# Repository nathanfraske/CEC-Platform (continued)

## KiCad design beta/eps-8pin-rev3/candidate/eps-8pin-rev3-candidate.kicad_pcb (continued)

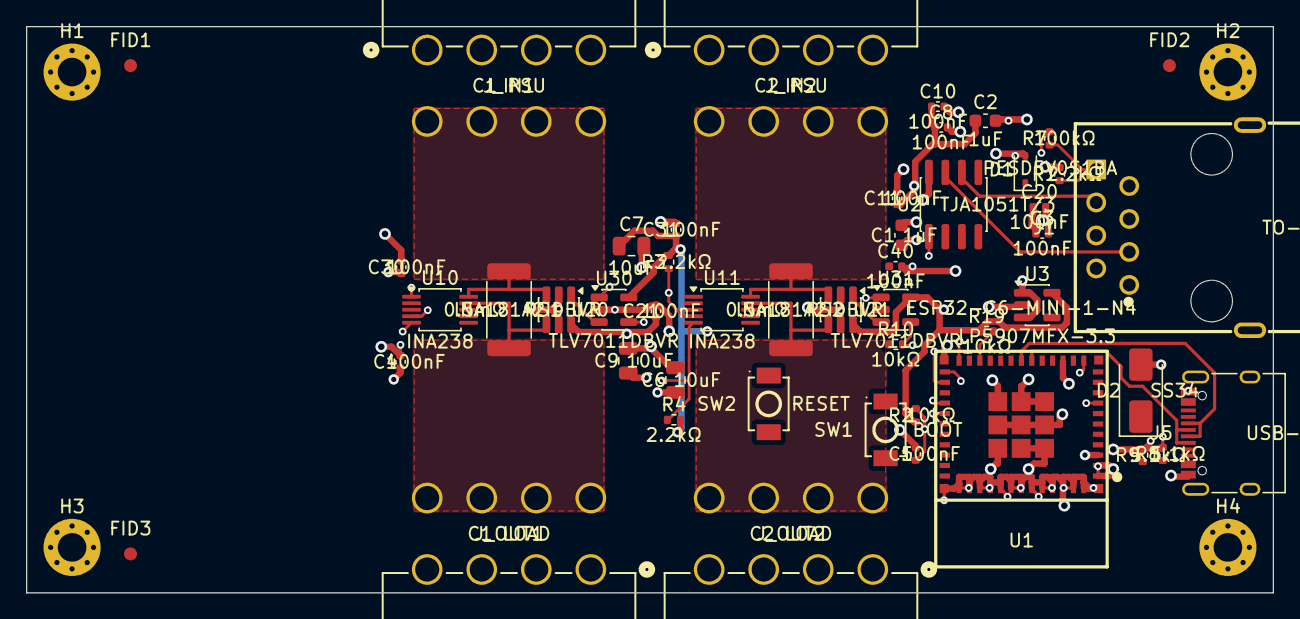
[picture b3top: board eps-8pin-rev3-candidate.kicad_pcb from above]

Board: 6 copper layers, 96.0 x 43.6 mm, 53 parts (0 on the bottom side), 29 nets.

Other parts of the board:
FID1, FID2, FID3: Fiducial_1mm_Mask2mm
H1, H2, H3, H4: MountingHole_2.2mm_M2_Pad_Via

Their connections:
GND: H1.1, H2.1, H3.1, H4.1; also elsewhere on the board

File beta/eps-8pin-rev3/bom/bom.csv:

Reference,Qty,Value,Footprint,MPN,Manufacturer,LCSC,LC_Stock,Chosen_Distributor,Datasheet,Validated,DNP,Notes
"C1,C2",2,1uF,C_0603_1608Metric,CL10A105KB8NNNC,Samsung,C15849,,,,,,
"C3,C4,C5,C8,C10,C11,C20,C21,C30,C31,C40",11,100nF,C_0402_1005Metric,CL05B104KO5NNNC,Samsung,C1525,,,,,,
"C6,C7,C9",3,10uF,C_0805_2012Metric,CL21A106KAYNNNE,Samsung,C15850,,,,,,
D1,1,PESD5V0S1BA,D_SOD-323,PESD5V0S1BA,HXY MOSFET,C5261083,,,https://www.lcsc.com/datasheet/C5261083.pdf,,,
D2,1,SS34,D_SMA,SS34,MDD,C8678,,,,,,
J1,1,TO-HUB,RJ45_FTP_Shielded_Horizontal,KH-RJ45-58-8P8C,Kinghelm,C2683360,,,https://www.lcsc.com/datasheet/C2683360.pdf,,,
J5,1,USB-C 2.0,USB_C_Receptacle_XKB_U262-16XN-4BVC11,U262-161N-4BVC11,XKB Connection,C319148,,,https://datasheet.lcsc.com/szlcsc/1811141824_XKB-Enterprise-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,,,
J_IN1,1,C1 PSU,Molex_Mini-Fit_Jr_87427-0802_2x04_P4.20mm_RA,87427-0802,Molex,,,,https://www.molex.com/content/dam/molex/molex-dot-com/produc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,,,
J_IN2,1,C2 PSU,Molex_Mini-Fit_Jr_87427-0802_2x04_P4.20mm_RA,87427-0802,Molex,,,,https://www.molex.com/content/dam/molex/molex-dot-com/produc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,,,
J_OUT1,1,C1 LOAD,Molex_Mini-Fit_Jr_87427-0802_2x04_P4.20mm_RA,87427-0802,Molex,,,,https://www.molex.com/content/dam/molex/molex-dot-com/produc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,,,
J_OUT2,1,C2 LOAD,Molex_Mini-Fit_Jr_87427-0802_2x04_P4.20mm_RA,87427-0802,Molex,,,,https://www.molex.com/content/dam/molex/molex-dot-com/produc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,,,
"R1,R3,R4",3,2.2kΩ,R_0402_1005Metric,0402WGF2201TCE,UNI-ROYAL,C25879,,,,,,
"R2,R10,R19",3,10kΩ,R_0402_1005Metric,0402WGF1002TCE,UNI-ROYAL,C25744,,,https://www.lcsc.com/product-detail/C25744.html,,,10 kohm follows Espressif ESP32-C6-DevKitC-1; GPIO8 must be high with GPIO9 low for joint download boot
R7,1,100kΩ,R_0402_1005Metric,0402WGF1003TCE,UNI-ROYAL,C25741,,,,,,
"R8,R9",2,5.1kΩ,R_0402_1005Metric,0402WGF5101TCE,UNI-ROYAL,C25905,,,,,,
"RS1,RS2",2,0.5mΩ,R_2512_6332Metric,CSS2H-2512R-L500F,Bourns,,,,https://www.bourns.com/docs/product-datasheets/css2h-2512.pdf,,,"OQ-11 locked selection on the single current EPS product: 0.5mOhm, CSS2H-2512R-L500F. Distributor availability remains a BOM-freeze check."
SW1,1,BOOT,TS-1088-AR02016,TS-1088-AR02016,XUNPU,C720477,,,https://www.lcsc.com/datasheet/C720477.pdf,,,
SW2,1,RESET,TS-1088-AR02016,TS-1088-AR02016,XUNPU,C720477,,,https://www.lcsc.com/datasheet/C720477.pdf,,,
U1,1,ESP32-C6-MINI-1-N4,ESP32-C6-MINI-1,ESP32-C6-MINI-1-N4,Espressif Systems,C5736265,,,https://documentation.espressif.com/esp32-c6-mini-1_mini-1u_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,,,
"U10,U11",2,INA238,VSSOP-10_3x3mm_P0.5mm,INA238AIDGSR,Texas Instruments,C2868250,,,https://www.ti.com/lit/ds/symlink/ina238.pdf,,,
U2,1,TJA1051T/3,SOIC-8_3.9x4.9mm_P1.27mm,TJA1051T/3/1J,NXP Semiconductors,C38695,,,https://www.nxp.com/docs/en/data-sheet/TJA1051.pdf,,,
"U20,U21",2,INA181A2IDBVR,SOT-23-6,INA181A2IDBVR,Texas Instruments,C2058784,,,https://www.ti.com/lit/ds/symlink/ina181.pdf,,,
U3,1,LP5907MFX-3.3,SOT-23-5,LP5907MFX-3.3/NOPB,Texas Instruments,C80670,,,https://www.ti.com/lit/ds/symlink/lp5907.pdf,,,
"U30,U31",2,TLV7011DBVR,SOT-23-5,TLV7011DBVR,Texas Instruments,C702117,,,https://www.ti.com/lit/ds/symlink/tlv7011.pdf,,,

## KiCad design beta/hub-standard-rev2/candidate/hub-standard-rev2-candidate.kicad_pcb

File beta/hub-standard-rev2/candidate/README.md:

# `candidate/`: the current best diagnostic board for this module

ONE board file, kept current by the wave (owner directive 2026-07-25: "the current
best should be placed into a candidate folder per board and kept current with only
one board ideally so we have a reference").

`<board>-candidate.kicad_pcb` (+ its `.kicad_pro` / `.kicad_dru` sidecars) is a COPY
of the best board the wave has ever published for this module, with `candidate.json`
recording where it came from and how it graded. Open it to see the real current
state of the layout without digging through `build/fresh-wave-*/`.

IMPORTANT: `candidate/` is a diagnostic-reference channel, not a release-acceptance
channel. A routed board remains here when its route gate fails so reviewers can see
and improve the best failure. `candidate.json` therefore records
`candidate_role: diagnostic-reference`, `release_accepted: false`, and the distinct
`route_gate_passed` result. Only the aggregate release pipeline may accept a board.

RULES the wave enforces on every publish:
  * SCHEMATIC FRESHNESS outranks score: a winner matching more of the CURRENT
    component signatures replaces the reference even on a worse score, and a
    staler board never replaces a fresher one. The signature covers value,
    footprint, and numbered-pad nets. `schematic_match` and `schematic_exact` in
    `candidate.json` record the result. A board that grades well but predates a
    schematic or footprint change is the worse reference;
  * otherwise it replaces this file only when the new winner BEATS the recorded
    `sort_key` (lower is better -- the same ranking the wave itself uses);
  * a board satisfying the CURRENT segmented-mezzanine geometry replaces one
    that violates it, independent of route score; an obsolete mechanical datum
    is stale in the same way an obsolete component signature is stale;
  * a routed winner always beats a placement-only one, and a placement-only winner
    NEVER overwrites a routed reference;
  * exactly one `.kicad_pcb` lives here -- stale board files are pruned.

`candidate.json` is also refreshable without publishing a board. Consumers that
use a candidate as a placement oracle or materialization template MUST require
`schematic_exact: true` after a current refresh. A stale candidate remains useful
for historical outline, connector, mount, and copper review, but it is not a
component-inventory or pin/net authority.

This is a REFERENCE, not the board of record: it is machine-written, so never hand-edit
it (edits are silently overwritten by the next better wave). The authoritative
schematic + the module's own project files stay in the parent directory.

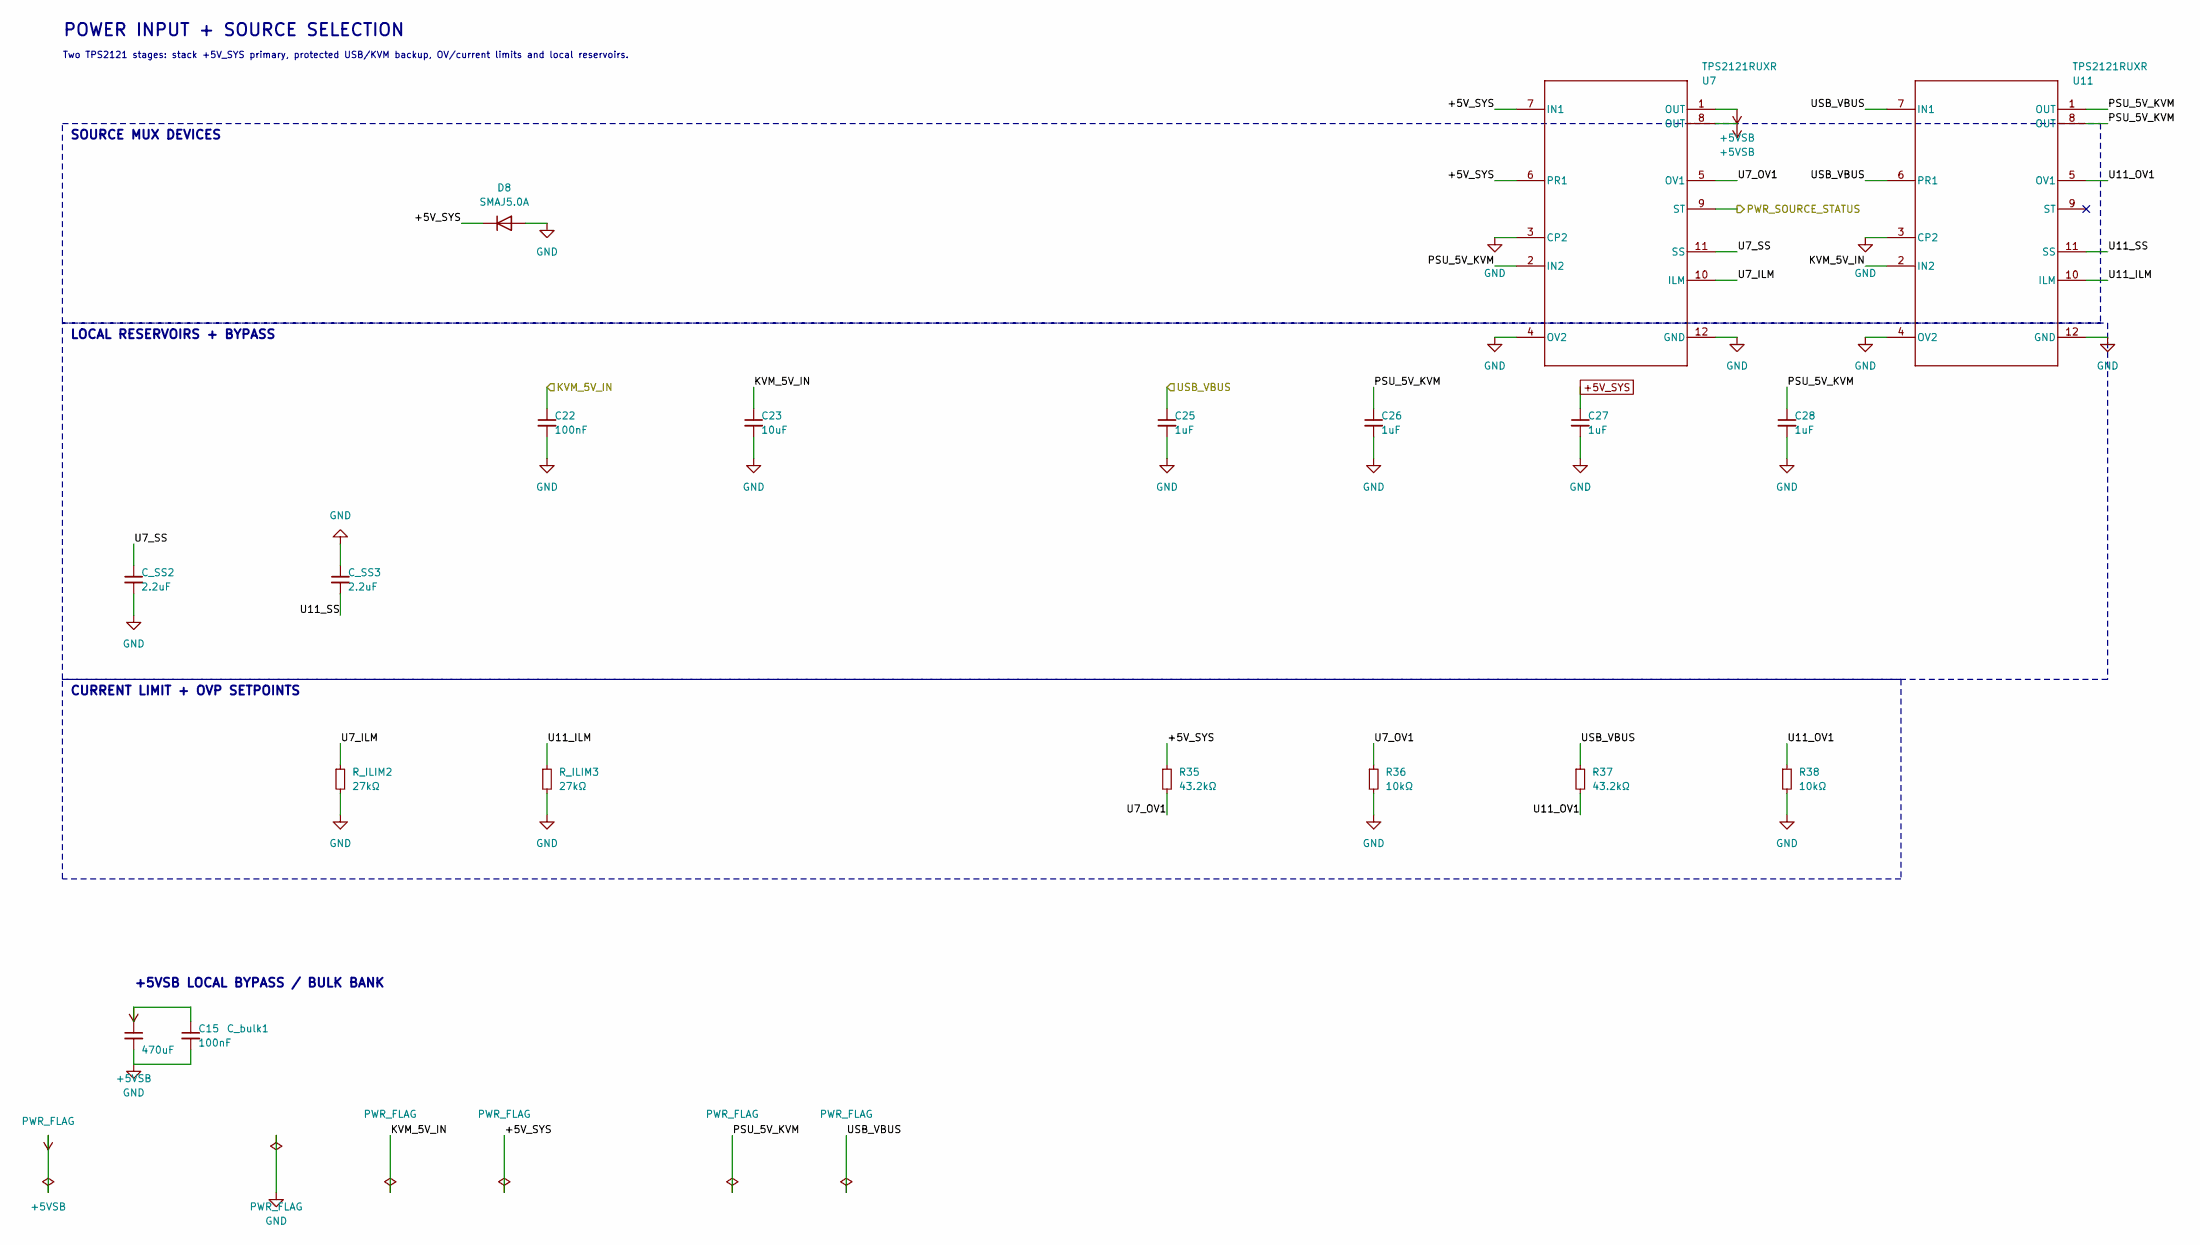
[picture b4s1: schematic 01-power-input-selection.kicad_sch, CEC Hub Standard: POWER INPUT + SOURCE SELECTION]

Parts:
C15, C22: 100nF; C_0402_1005Metric; MPN CL05B104KO5NNNC; LCSC C1525
C23: 10uF; C_0603_1608Metric; MPN CL10A106MA8NRNC; LCSC C96446
C25, C26, C27, C28: 1uF; C_0603_1608Metric; MPN CL10A105KB8NNNC; LCSC C15849
C_SS2, C_SS3: 2.2uF; C_0603_1608Metric; MPN CL10A225KO8NNNC; LCSC C23630
C_bulk1: 470uF; CP_Elec_6.3x7.7; MPN RVT1A471M0607; LCSC C335982
D8: SMAJ5.0A; D_SMA; MPN SMAJ5.0A; LCSC C113952
R35, R37: 43.2kΩ; R_0402_1005Metric; MPN 0402WGF4322TCE; LCSC C25894
R36, R38: 10kΩ; R_0402_1005Metric; MPN 0402WGF1002TCE; LCSC C25744
R_ILIM2, R_ILIM3: 27kΩ; R_0402_1005Metric; MPN 0402WGF2702TCE; LCSC C25771
U7, U11: TPS2121RUXR; RUX0012A; MPN TPS2121RUXR; LCSC C485916

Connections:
+5VSB: C15.1, C_bulk1.1, U7.1 (OUT), U7.8 (OUT); also elsewhere on the board
+5V_SYS: C27.1, D8.1 (K), R35.1, U7.6 (PR1), U7.7 (IN1); also elsewhere on the board
/KVM_5V_IN: C22.1, C23.1, U11.2 (IN2); also elsewhere on the board
/POWER INPUT + SOURCE SELECTION/PSU_5V_KVM: C26.1, C28.1, U7.2 (IN2), U11.1 (OUT), U11.8 (OUT)
/POWER INPUT + SOURCE SELECTION/U7_ILM: R_ILIM2.1, U7.10 (ILM)
/POWER INPUT + SOURCE SELECTION/U7_OV1: R35.2, R36.1, U7.5 (OV1)
/POWER INPUT + SOURCE SELECTION/U7_SS: C_SS2.1, U7.11 (SS)
/POWER INPUT + SOURCE SELECTION/U11_ILM: R_ILIM3.1, U11.10 (ILM)
/POWER INPUT + SOURCE SELECTION/U11_OV1: R37.2, R38.1, U11.5 (OV1)
/POWER INPUT + SOURCE SELECTION/U11_SS: C_SS3.2, U11.11 (SS)
/PWR_SOURCE_STATUS: U7.9 (ST); also elsewhere on the board
/USB_VBUS: C25.1, R37.1, U11.6 (PR1), U11.7 (IN1); also elsewhere on the board

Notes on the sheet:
POWER INPUT + SOURCE SELECTION
Two TPS2121 stages: stack +5V_SYS primary, protected USB/KVM backup, OV/current limits and local reservoirs.
+5VSB LOCAL BYPASS / BULK BANK
SOURCE MUX DEVICES
LOCAL RESERVOIRS + BYPASS
CURRENT LIMIT + OVP SETPOINTS

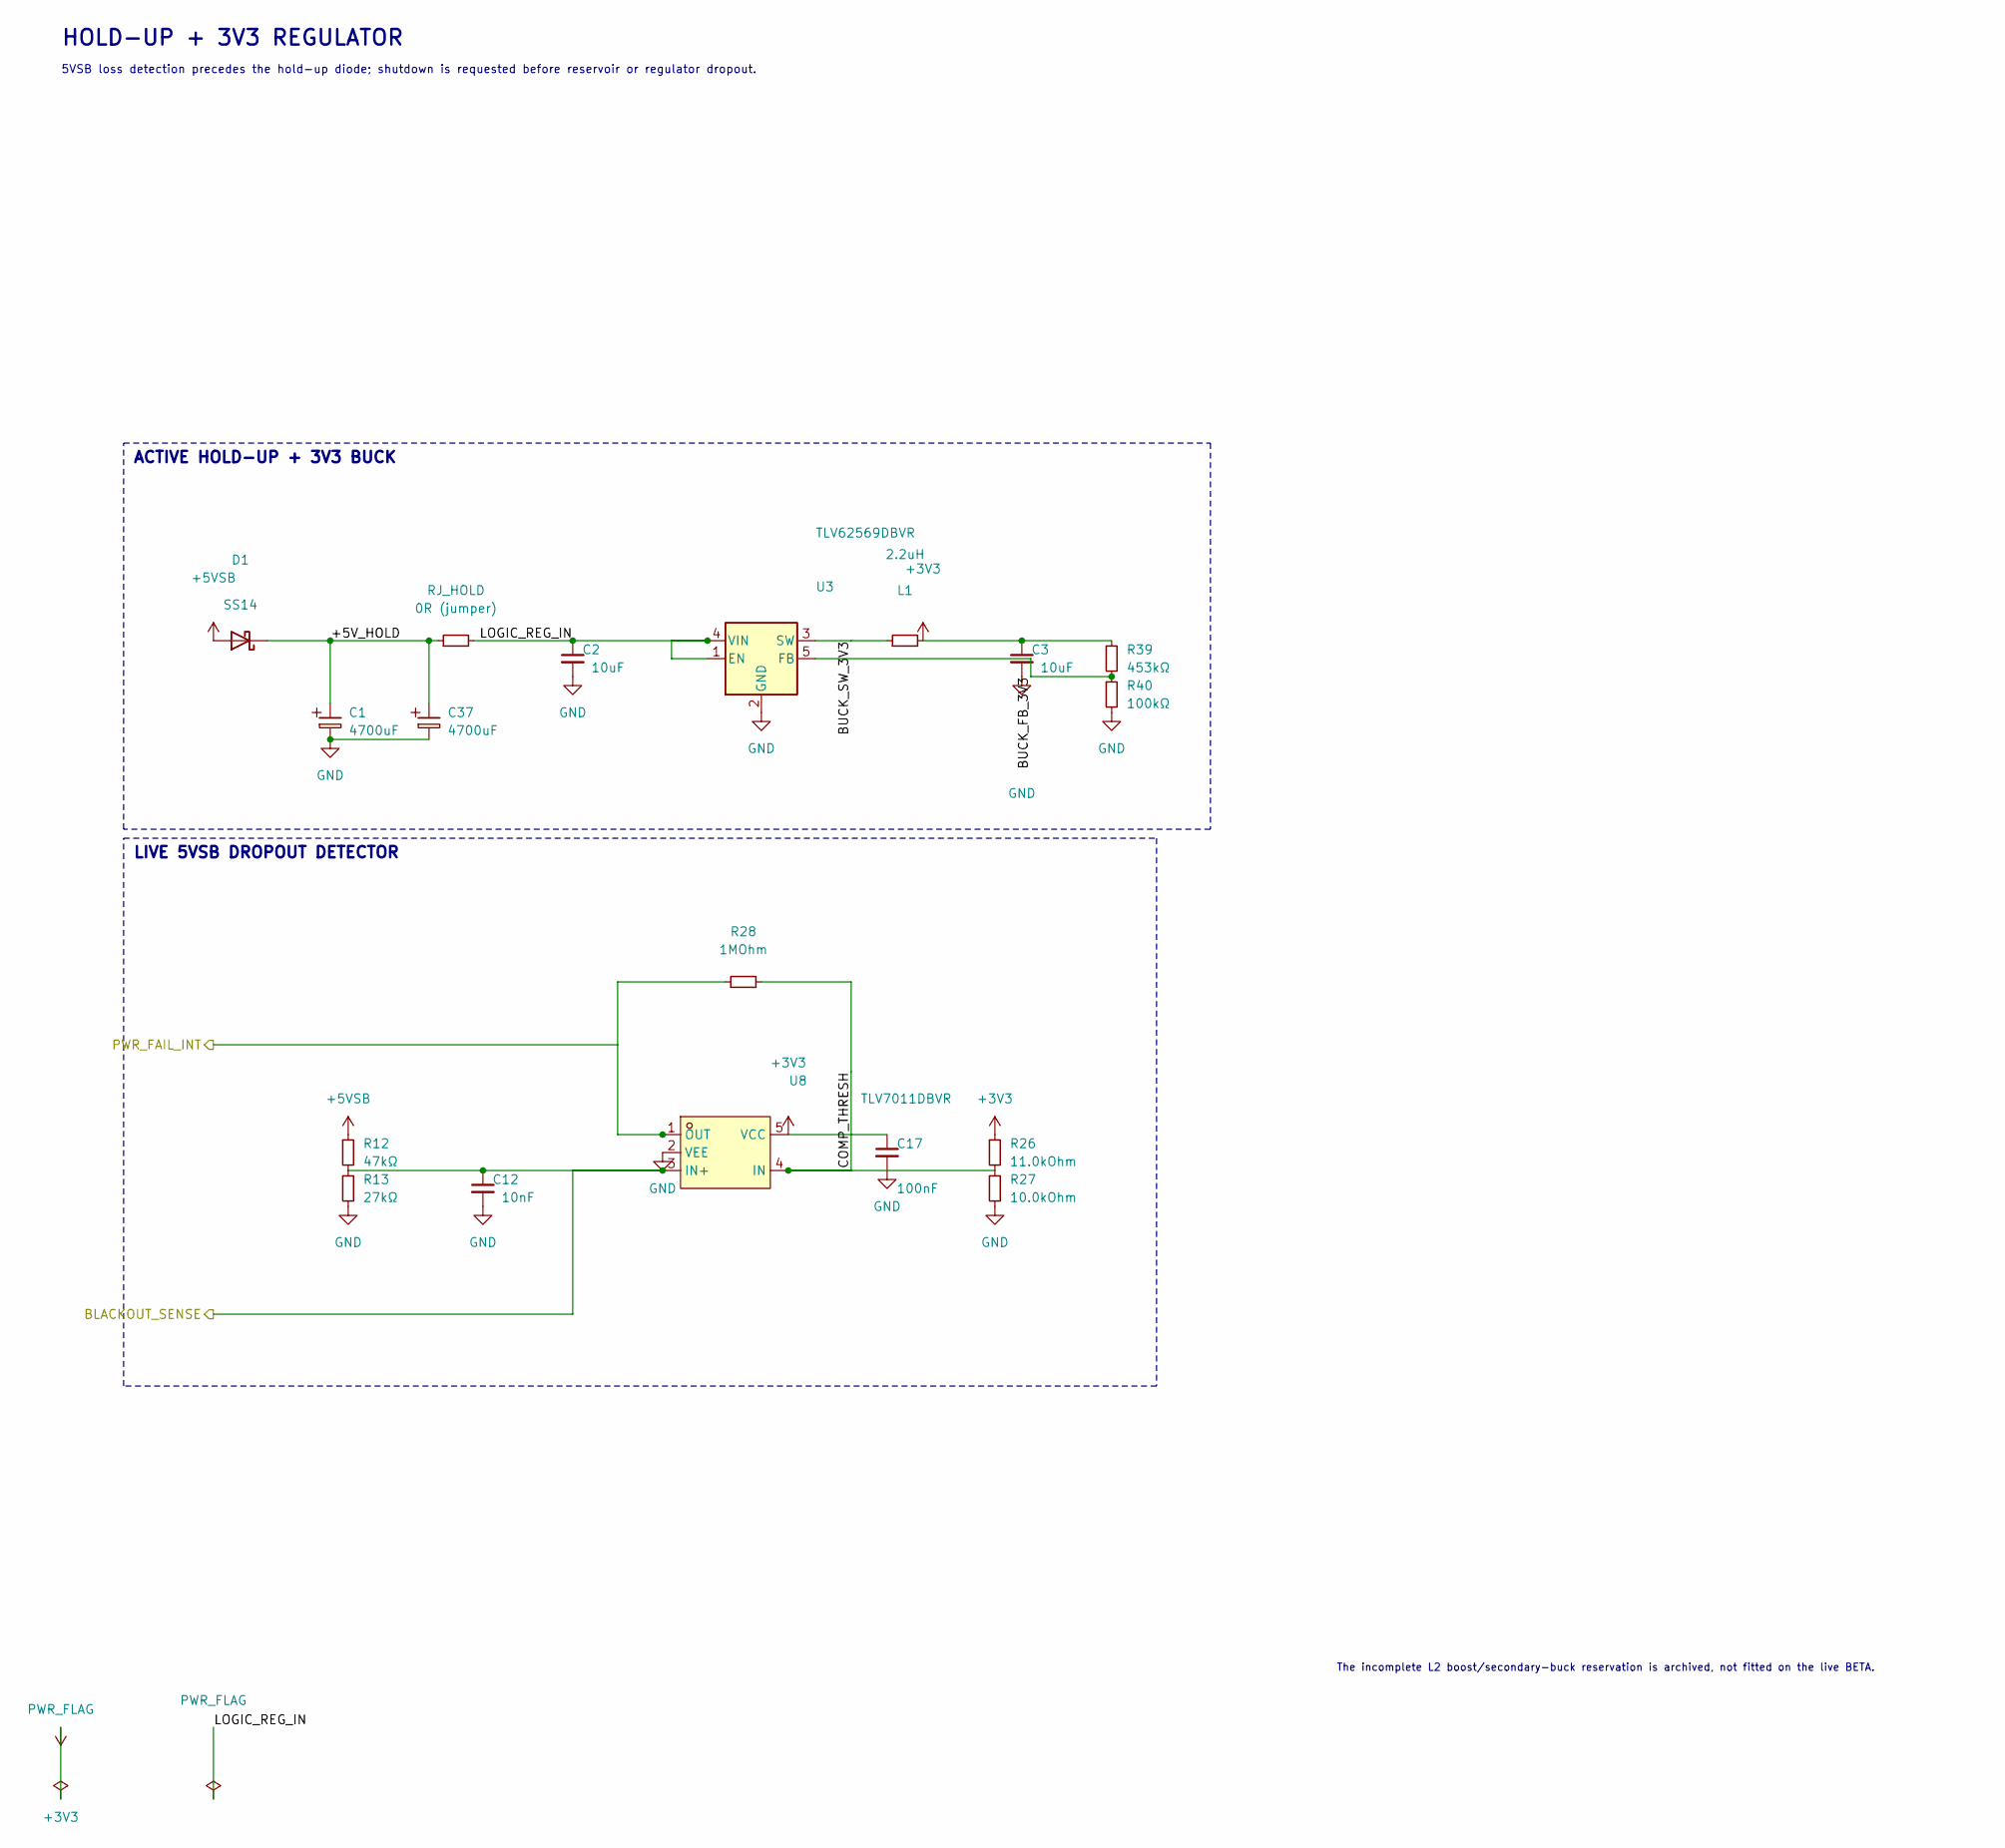
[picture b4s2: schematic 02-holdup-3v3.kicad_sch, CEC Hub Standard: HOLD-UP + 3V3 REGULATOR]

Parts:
C1, C37: 4700uF; CP_Elec_Lelon_VZH_18x16.5; MPN VZH472M1CTR-1816; LCSC C249940
C2, C3: 10uF; C_0603_1608Metric; MPN CL10A106MA8NRNC; LCSC C96446
C12: 10nF; C_0402_1005Metric; MPN CL05B103KB5NNNC; LCSC C15195
C17: 100nF; C_0402_1005Metric; MPN CL05B104KO5NNNC; LCSC C1525
D1: SS14; D_SMA; MPN SS14; LCSC C2480
L1: 2.2uH; VLS252010HBX-2R2M-1; MPN VLS252010HBX-2R2M-1; LCSC C88527
R12: 47kΩ; R_0402_1005Metric; MPN 0402WGF4702TCE; LCSC C25792
R13: 27kΩ; R_0402_1005Metric; MPN 0402WGF2702TCE; LCSC C25771
R26: 11.0kOhm; R_0402_1005Metric; MPN RC0402FR-0711KL; LCSC C138063
R27: 10.0kOhm; R_0402_1005Metric; MPN 0402WGF1002TCE; LCSC C25744
R28: 1MOhm; R_0402_1005Metric; MPN 0402WGF1004TCE; LCSC C26083
R39: 453kΩ; R_0402_1005Metric; MPN 0402WGF4533TCE; LCSC C27009
R40: 100kΩ; R_0402_1005Metric; MPN 0402WGF1003TCE; LCSC C25741
RJ_HOLD: 0R (jumper); R_0402_1005Metric; MPN 0402WGF0000TCE; LCSC C17168
U3: TLV62569DBVR; SOT-23-5_L3.0-W1.7-P0.95-LS2.8-BL; MPN TLV62569DBVR; LCSC C141836
U8: TLV7011DBVR; SOT-23-5; MPN TLV7011DBVR; LCSC C702117

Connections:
+3V3: C3.1, C17.1, L1.2, R26.1, R39.1, U8.5 (VCC); also elsewhere on the board
+5VSB: D1.2 (A), R12.1; also elsewhere on the board
/BLACKOUT_SENSE: C12.1, R12.2, R13.1, U8.3 (IN+); also elsewhere on the board
/HOLD-UP + 3V3 REGULATOR/+5V_HOLD: C1.1 (+), C37.1 (+), D1.1 (K), RJ_HOLD.1
/HOLD-UP + 3V3 REGULATOR/BUCK_FB_3V3: R39.2, R40.1, U3.5 (FB)
/HOLD-UP + 3V3 REGULATOR/BUCK_SW_3V3: L1.1, U3.3 (SW)
/HOLD-UP + 3V3 REGULATOR/LOGIC_REG_IN: C2.1, RJ_HOLD.2, U3.1 (EN), U3.4 (VIN)
/PWR_FAIL_INT: R28.1, U8.1 (OUT); also elsewhere on the board

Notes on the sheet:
HOLD-UP + 3V3 REGULATOR
5VSB loss detection precedes the hold-up diode; shutdown is requested before reservoir or regulator dropout.
The incomplete L2 boost/secondary-buck reservation is archived, not fitted on the live BETA.
ACTIVE HOLD-UP + 3V3 BUCK
LIVE 5VSB DROPOUT DETECTOR

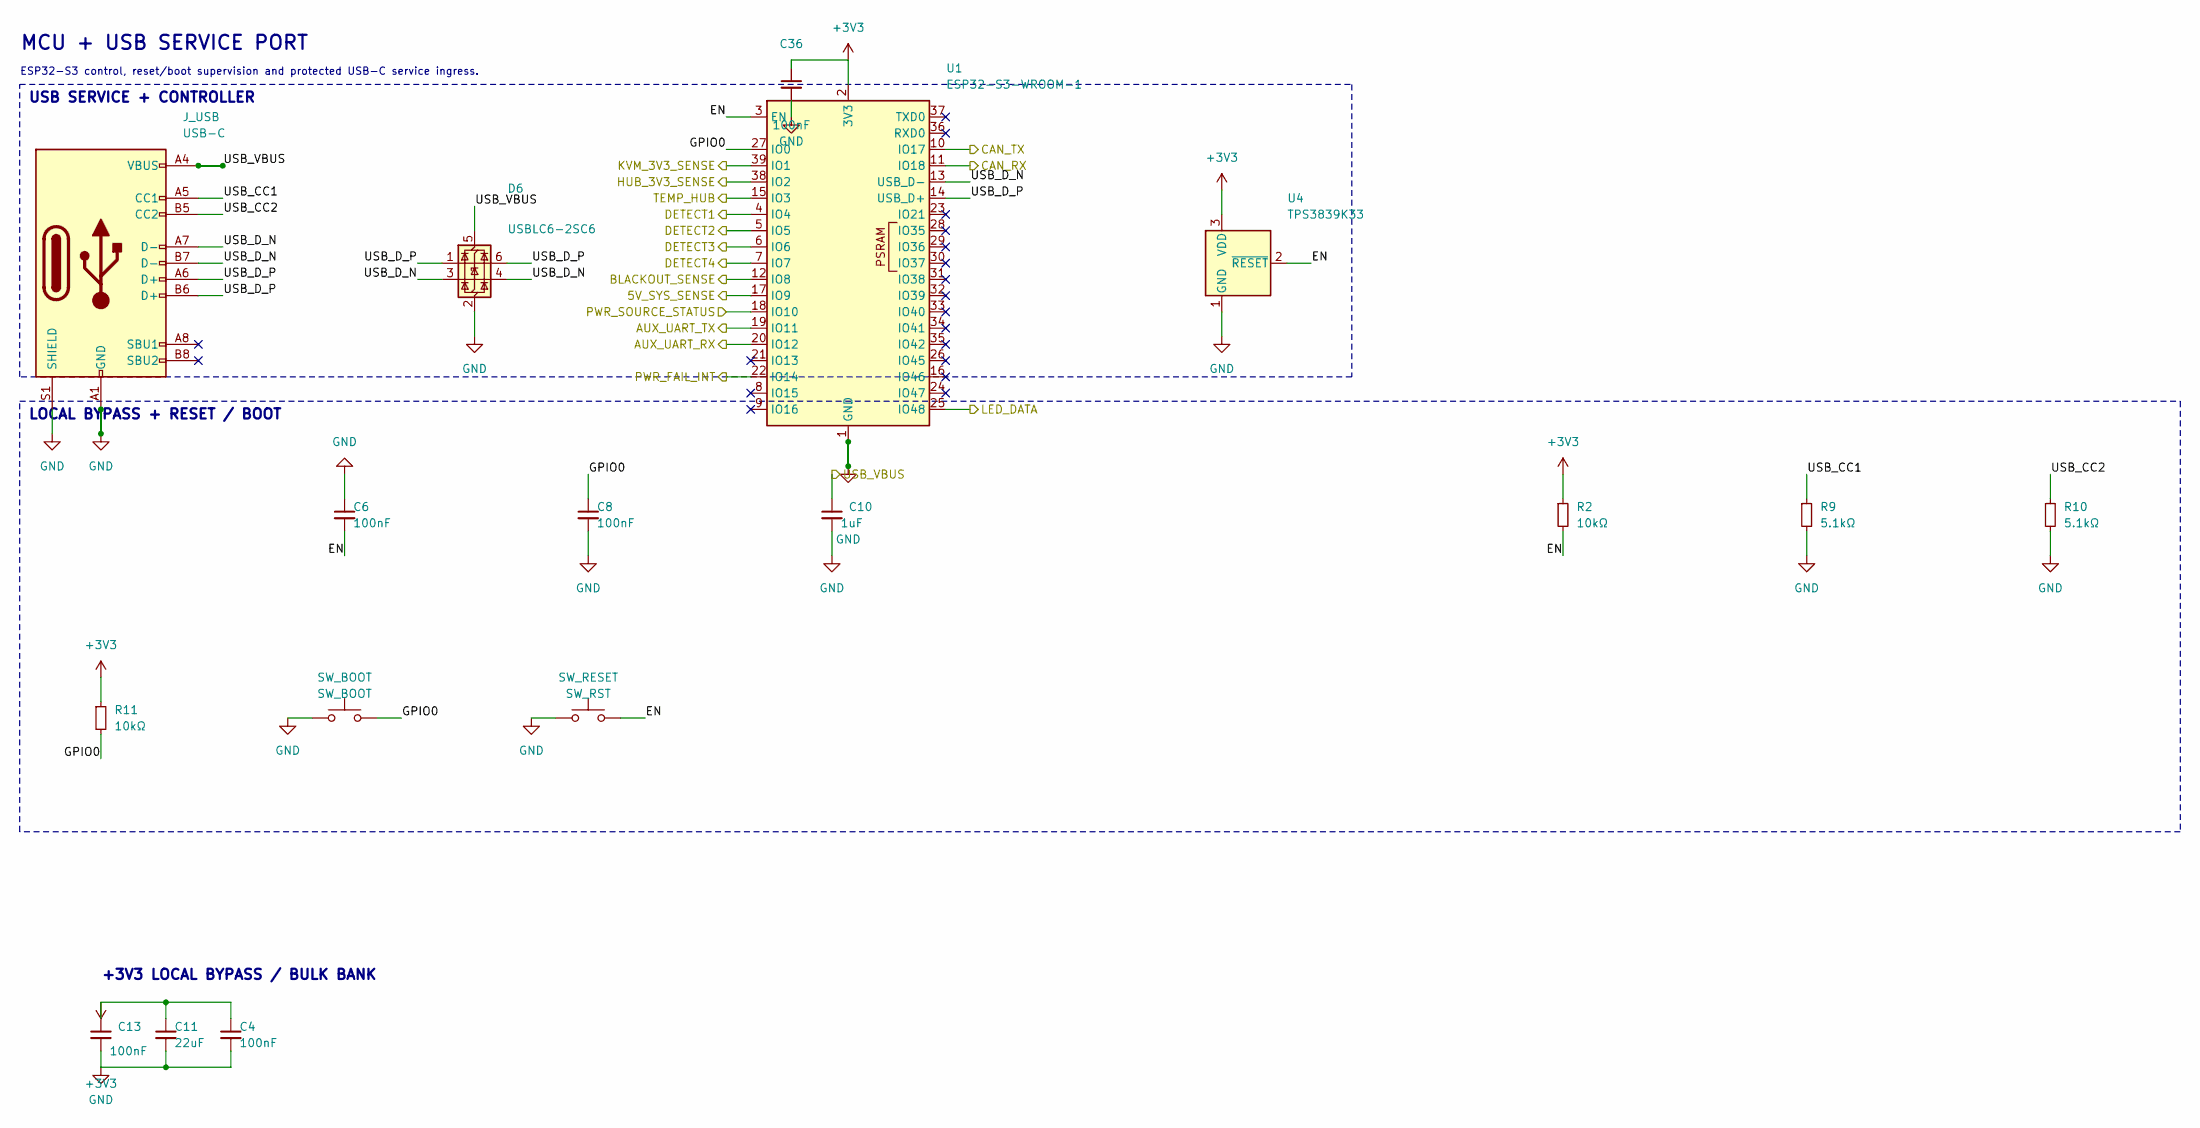
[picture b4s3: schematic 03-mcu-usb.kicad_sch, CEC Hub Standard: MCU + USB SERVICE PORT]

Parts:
C4, C6, C8, C13, C36: 100nF; C_0402_1005Metric; MPN CL05B104KO5NNNC; LCSC C1525
C10: 1uF; C_0603_1608Metric; MPN CL10A105KB8NNNC; LCSC C15849
C11: 22uF; C_0603_1608Metric; MPN CL10A226MP8NUNE; LCSC C86295
D6: USBLC6-2SC6; SOT-23-6; MPN USBLC6-2SC6; LCSC C2687116
J_USB: USB-C; USB_C_Receptacle_GCT_USB4215-03-A; MPN USB4215-03-A; LCSC C37616412
R2, R11: 10kΩ; R_0402_1005Metric; MPN 0402WGF1002TCE; LCSC C25744
R9, R10: 5.1kΩ; R_0402_1005Metric; MPN 0402WGF5101TCE; LCSC C25905
SW_BOOT: SW_BOOT; TS-1088-AR02016; MPN TS-1088-AR02016; LCSC C720477
SW_RESET: SW_RST; TS-1088-AR02016; MPN TS-1088-AR02016; LCSC C720477
U1: ESP32-S3-WROOM-1; ESP32-S3-WROOM-1_NoAntKeepout; MPN ESP32-S3-WROOM-1-N16R8; LCSC C2913202
U4: TPS3839K33; SOT-23; MPN TPS3839K33DBZR; LCSC C96333

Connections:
+3V3: C4.1, C11.1, C13.1, C36.1, R2.1, R11.1, U1.2 (3V3), U4.3 (VDD); also elsewhere on the board
/5V_SYS_SENSE: U1.17 (IO9); also elsewhere on the board
/AUX_UART_RX: U1.20 (IO12); also elsewhere on the board
/AUX_UART_TX: U1.19 (IO11); also elsewhere on the board
/BLACKOUT_SENSE: U1.12 (IO8); also elsewhere on the board
/CAN_RX: U1.11 (IO18); also elsewhere on the board
/CAN_TX: U1.10 (IO17); also elsewhere on the board
/DETECT1: U1.4 (IO4); also elsewhere on the board
/DETECT2: U1.5 (IO5); also elsewhere on the board
/DETECT3: U1.6 (IO6); also elsewhere on the board
/DETECT4: U1.7 (IO7); also elsewhere on the board
/HUB_3V3_SENSE: U1.38 (IO2); also elsewhere on the board
/KVM_3V3_SENSE: U1.39 (IO1); also elsewhere on the board
/LED_DATA: U1.25 (IO48); also elsewhere on the board
/MCU + USB SERVICE PORT/EN: C6.2, R2.2, SW_RESET.2, U1.3 (EN), U4.2 (~RESET)
/MCU + USB SERVICE PORT/GPIO0: C8.1, R11.2, SW_BOOT.2, U1.27 (IO0)
/MCU + USB SERVICE PORT/USB_CC1: J_USB.A5 (CC1), R9.1
/MCU + USB SERVICE PORT/USB_CC2: J_USB.B5 (CC2), R10.1
/MCU + USB SERVICE PORT/USB_D_N: D6.3 (I/O2), D6.4 (I/O2), J_USB.A7 (D-), J_USB.B7 (D-), U1.13 (USB_D-)
/MCU + USB SERVICE PORT/USB_D_P: D6.1 (I/O1), D6.6 (I/O1), J_USB.A6 (D+), J_USB.B6 (D+), U1.14 (USB_D+)
/PWR_FAIL_INT: U1.22 (IO14); also elsewhere on the board
/PWR_SOURCE_STATUS: U1.18 (IO10); also elsewhere on the board
/TEMP_HUB: U1.15 (IO3); also elsewhere on the board
/USB_VBUS: C10.1, D6.5 (VBUS), J_USB.A4 (VBUS), J_USB.A9 (VBUS), J_USB.B4 (VBUS), J_USB.B9 (VBUS); also elsewhere on the board

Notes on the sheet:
MCU + USB SERVICE PORT
ESP32-S3 control, reset/boot supervision and protected USB-C service ingress.
+3V3 LOCAL BYPASS / BULK BANK
USB SERVICE + CONTROLLER
LOCAL BYPASS + RESET / BOOT

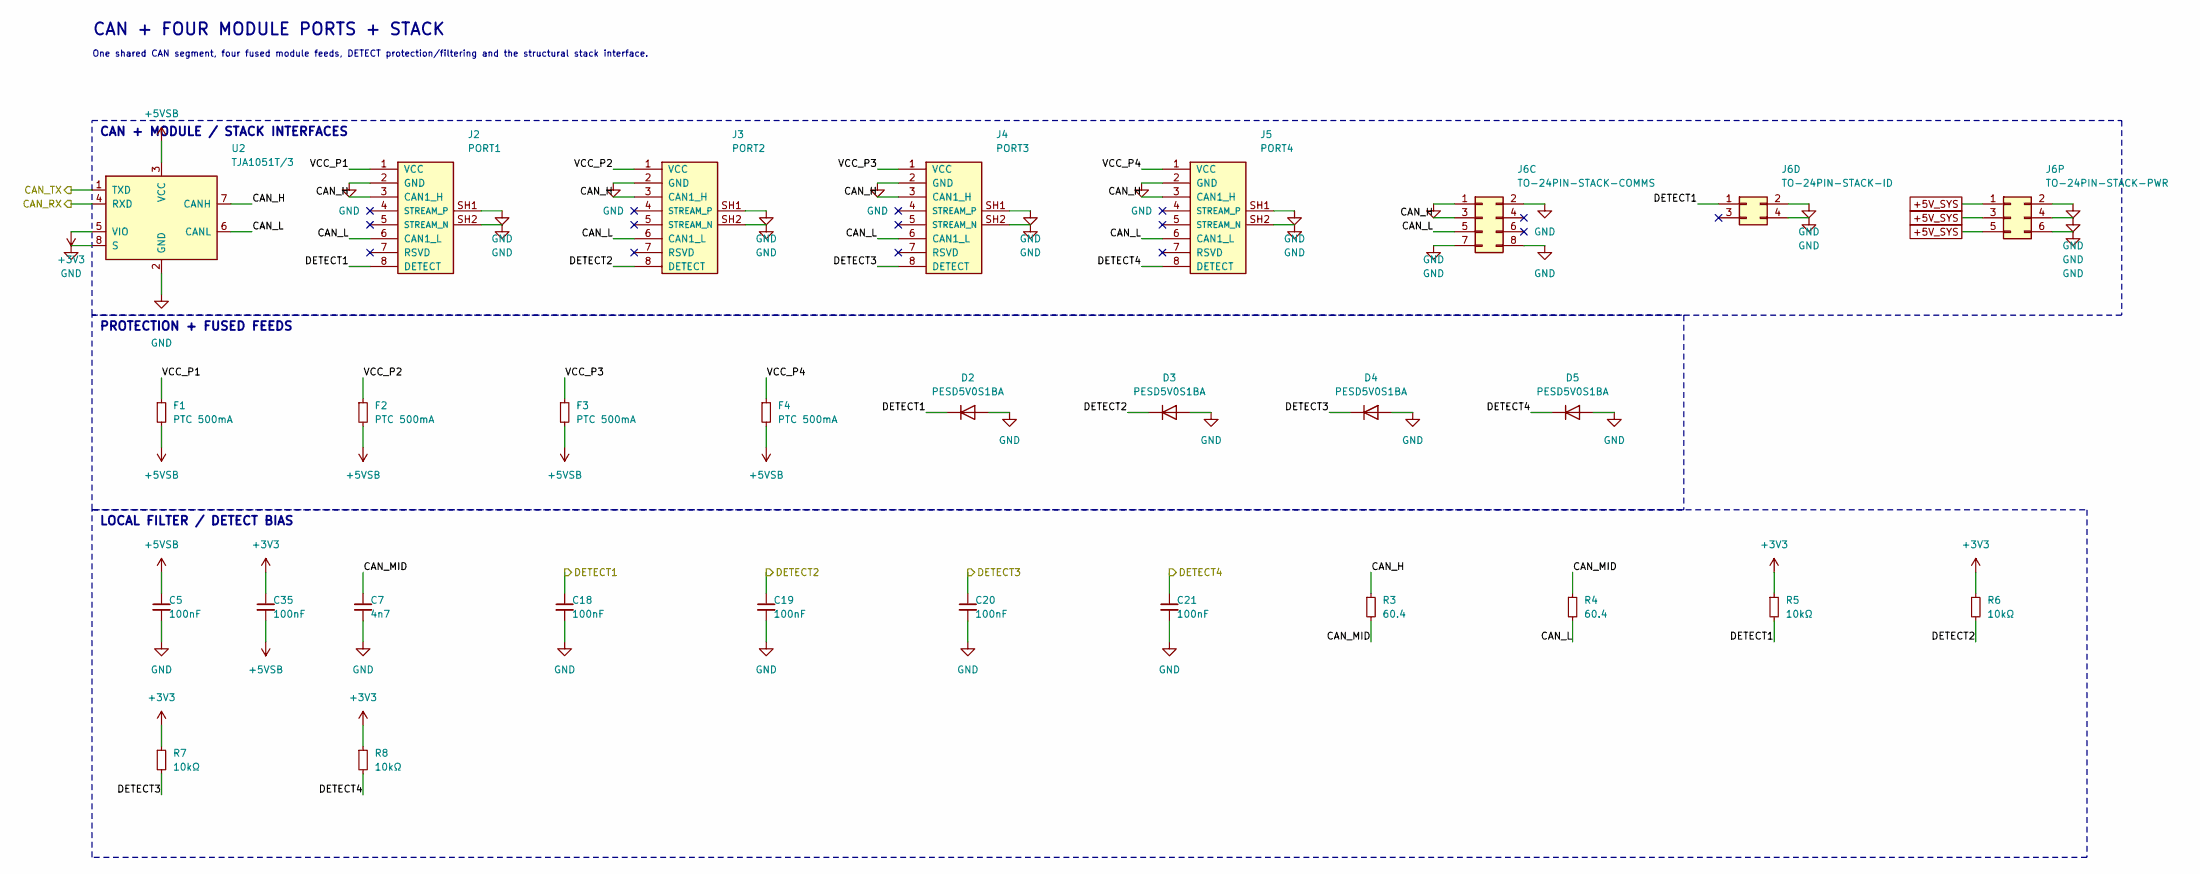
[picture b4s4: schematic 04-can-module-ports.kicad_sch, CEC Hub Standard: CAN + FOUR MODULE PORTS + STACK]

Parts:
C5, C18, C19, C20, C21, C35: 100nF; C_0402_1005Metric; MPN CL05B104KO5NNNC; LCSC C1525
C7: 4n7; C_0402_1005Metric; MPN 0402B472K500NT; LCSC C1538
D2, D3, D4, D5: PESD5V0S1BA; D_SOD-323; MPN PESD5V0S1BA; LCSC C5261083
F1, F2, F3, F4: PTC 500mA; R_0805_2012Metric; MPN SMD0805-050-6; LCSC C46640983
J2: PORT1; RJ45_FTP_Shielded_Horizontal; MPN KH-RJ45-58-8P8C; LCSC C2683360
J3: PORT2; RJ45_FTP_Shielded_Horizontal; MPN KH-RJ45-58-8P8C; LCSC C2683360
J4: PORT3; RJ45_FTP_Shielded_Horizontal; MPN KH-RJ45-58-8P8C; LCSC C2683360
J5: PORT4; RJ45_FTP_Shielded_Horizontal; MPN KH-RJ45-58-8P8C; LCSC C2683360
J6C: TO-24PIN-STACK-COMMS; PinSocket_2x04_P2.54mm_Vertical; MPN SSQ-104-01-G-D
J6D: TO-24PIN-STACK-ID; PinSocket_2x02_P2.54mm_Vertical; MPN SSQ-102-01-G-D
J6P: TO-24PIN-STACK-PWR; PinSocket_2x03_P2.54mm_Vertical; MPN SSQ-103-01-G-D
R3, R4: 60.4; R_0402_1005Metric; MPN GR0402F60R4TAG00; LCSC C49654185
R5, R6, R7, R8: 10kΩ; R_0402_1005Metric; MPN 0402WGF1002TCE; LCSC C25744
U2: TJA1051T/3; SOIC-8_3.9x4.9mm_P1.27mm; MPN TJA1051T/3/1J; LCSC C38695

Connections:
+3V3: C35.1, R5.1, R6.1, R7.1, R8.1, U2.5 (VIO); also elsewhere on the board
+5VSB: C5.1, C35.2, F1.2, F2.2, F3.2, F4.2, U2.3 (VCC); also elsewhere on the board
+5V_SYS: J6P.1, J6P.3, J6P.5; also elsewhere on the board
/CAN + FOUR MODULE PORTS + STACK/CAN_H: J2.3 (CAN1_H), J3.3 (CAN1_H), J4.3 (CAN1_H), J5.3 (CAN1_H), J6C.3, R3.1, U2.7 (CANH)
/CAN + FOUR MODULE PORTS + STACK/CAN_L: J2.6 (CAN1_L), J3.6 (CAN1_L), J4.6 (CAN1_L), J5.6 (CAN1_L), J6C.5, R4.2, U2.6 (CANL)
/CAN + FOUR MODULE PORTS + STACK/CAN_MID: C7.1, R3.2, R4.1
/CAN + FOUR MODULE PORTS + STACK/VCC_P1: F1.1, J2.1 (VCC)
/CAN + FOUR MODULE PORTS + STACK/VCC_P2: F2.1, J3.1 (VCC)
/CAN + FOUR MODULE PORTS + STACK/VCC_P3: F3.1, J4.1 (VCC)
/CAN + FOUR MODULE PORTS + STACK/VCC_P4: F4.1, J5.1 (VCC)
/CAN_RX: U2.4 (RXD); also elsewhere on the board
/CAN_TX: U2.1 (TXD); also elsewhere on the board
/DETECT1: C18.1, D2.1 (K), J2.8 (DETECT), J6D.1, R5.2; also elsewhere on the board
/DETECT2: C19.1, D3.1 (K), J3.8 (DETECT), R6.2; also elsewhere on the board
/DETECT3: C20.1, D4.1 (K), J4.8 (DETECT), R7.2; also elsewhere on the board
/DETECT4: C21.1, D5.1 (K), J5.8 (DETECT), R8.2; also elsewhere on the board

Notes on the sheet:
CAN + FOUR MODULE PORTS + STACK
One shared CAN segment, four fused module feeds, DETECT protection/filtering and the structural stack interface.
CAN + MODULE / STACK INTERFACES
PROTECTION + FUSED FEEDS
LOCAL FILTER / DETECT BIAS

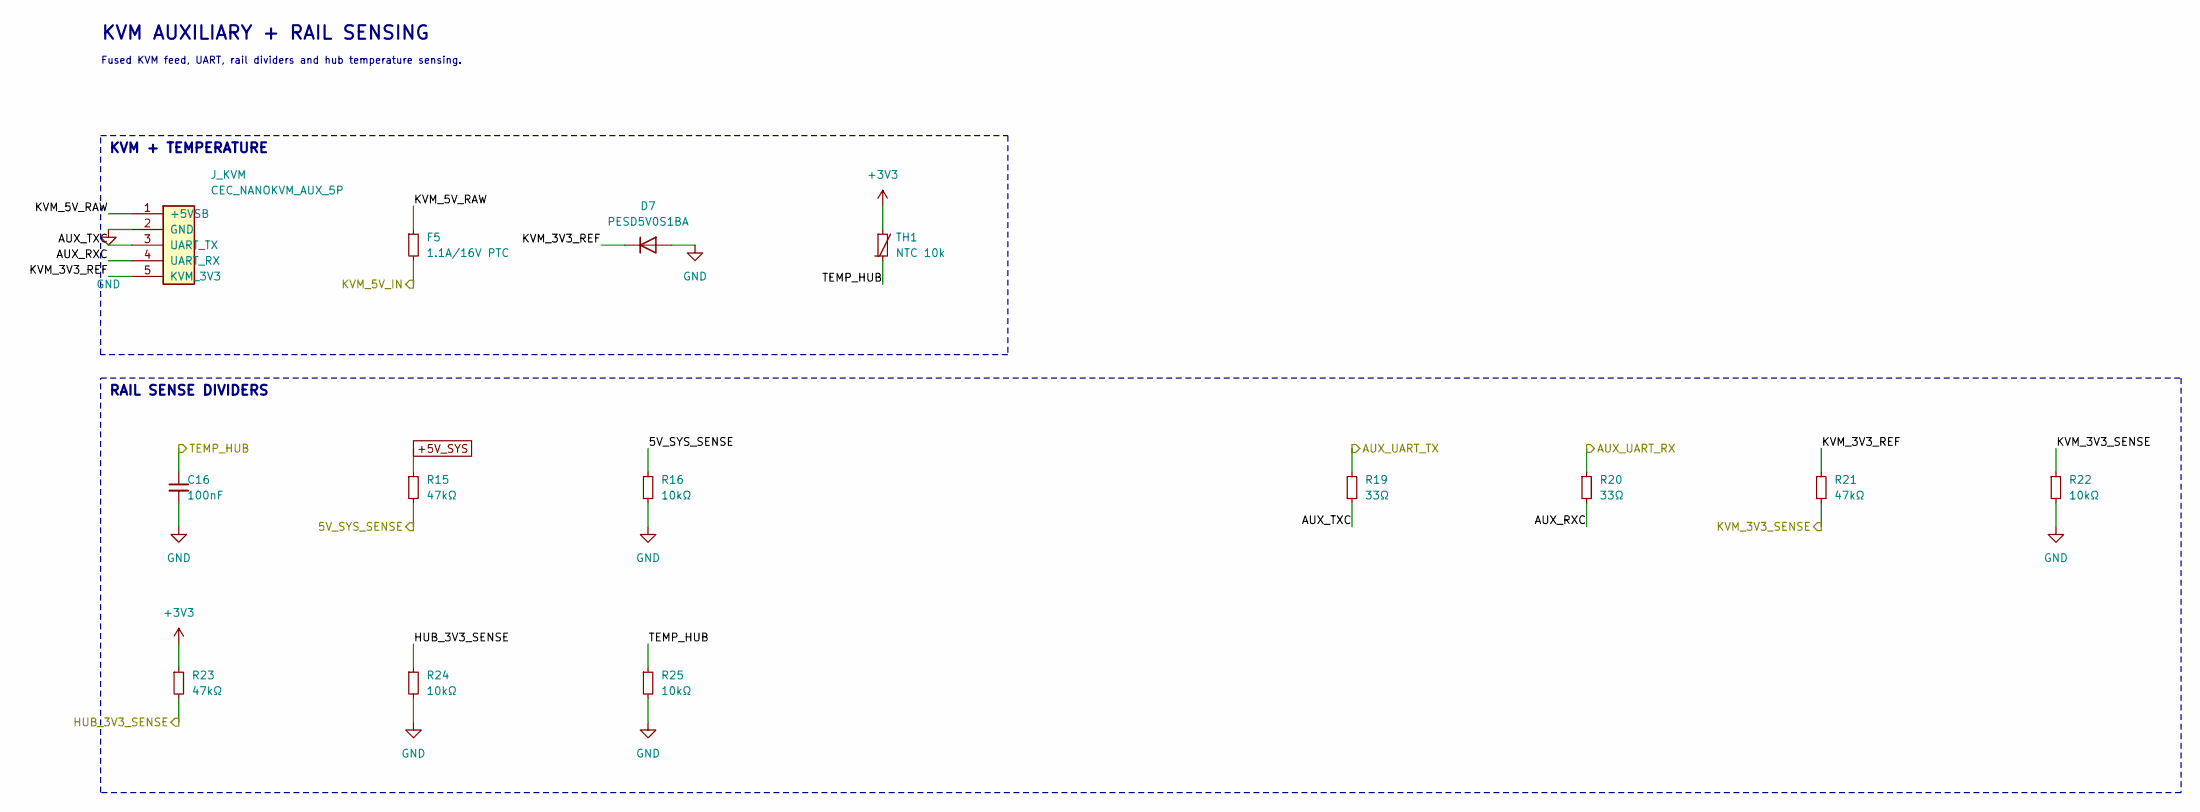
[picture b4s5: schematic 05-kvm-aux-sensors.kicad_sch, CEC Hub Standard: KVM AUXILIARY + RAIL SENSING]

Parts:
C16: 100nF; C_0402_1005Metric; MPN CL05B104KO5NNNC; LCSC C1525
D7: PESD5V0S1BA; D_SOD-323; MPN PESD5V0S1BA; LCSC C5261083
F5: 1.1A/16V PTC; R_1206_3216Metric; MPN FSMD110-16-1206R; LCSC C5707763
J_KVM: CEC_NANOKVM_AUX_5P; JST_PH_S5B-PH-K-S_1x05_P2.00mm_Horizontal; MPN S5B-PH-K-S(LF)(SN); LCSC C157923
R15, R21, R23: 47kΩ; R_0402_1005Metric; MPN 0402WGF4702TCE; LCSC C25792
R16, R22, R24, R25: 10kΩ; R_0402_1005Metric; MPN 0402WGF1002TCE; LCSC C25744
R19, R20: 33Ω; R_0402_1005Metric; MPN 0402WGF330JTCE; LCSC C25105
TH1: NTC 10k; NTC_0402_1005Metric; MPN NCP15XH103F03RC; LCSC C77131

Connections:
+3V3: R23.1, TH1.1; also elsewhere on the board
+5V_SYS: R15.1; also elsewhere on the board
/5V_SYS_SENSE: R15.2, R16.1; also elsewhere on the board
/AUX_UART_RX: R20.1; also elsewhere on the board
/AUX_UART_TX: R19.1; also elsewhere on the board
/HUB_3V3_SENSE: R23.2, R24.1; also elsewhere on the board
/KVM AUXILIARY + RAIL SENSING/AUX_RXC: J_KVM.4 (UART_RX), R20.2
/KVM AUXILIARY + RAIL SENSING/AUX_TXC: J_KVM.3 (UART_TX), R19.2
/KVM AUXILIARY + RAIL SENSING/KVM_3V3_REF: D7.1 (K), J_KVM.5 (KVM_3V3), R21.1
/KVM AUXILIARY + RAIL SENSING/KVM_5V_RAW: F5.1, J_KVM.1 (+5VSB)
/KVM_3V3_SENSE: R21.2, R22.1; also elsewhere on the board
/KVM_5V_IN: F5.2; also elsewhere on the board
/TEMP_HUB: C16.1, R25.1, TH1.2; also elsewhere on the board

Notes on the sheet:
KVM AUXILIARY + RAIL SENSING
Fused KVM feed, UART, rail dividers and hub temperature sensing.
KVM + TEMPERATURE
RAIL SENSE DIVIDERS
